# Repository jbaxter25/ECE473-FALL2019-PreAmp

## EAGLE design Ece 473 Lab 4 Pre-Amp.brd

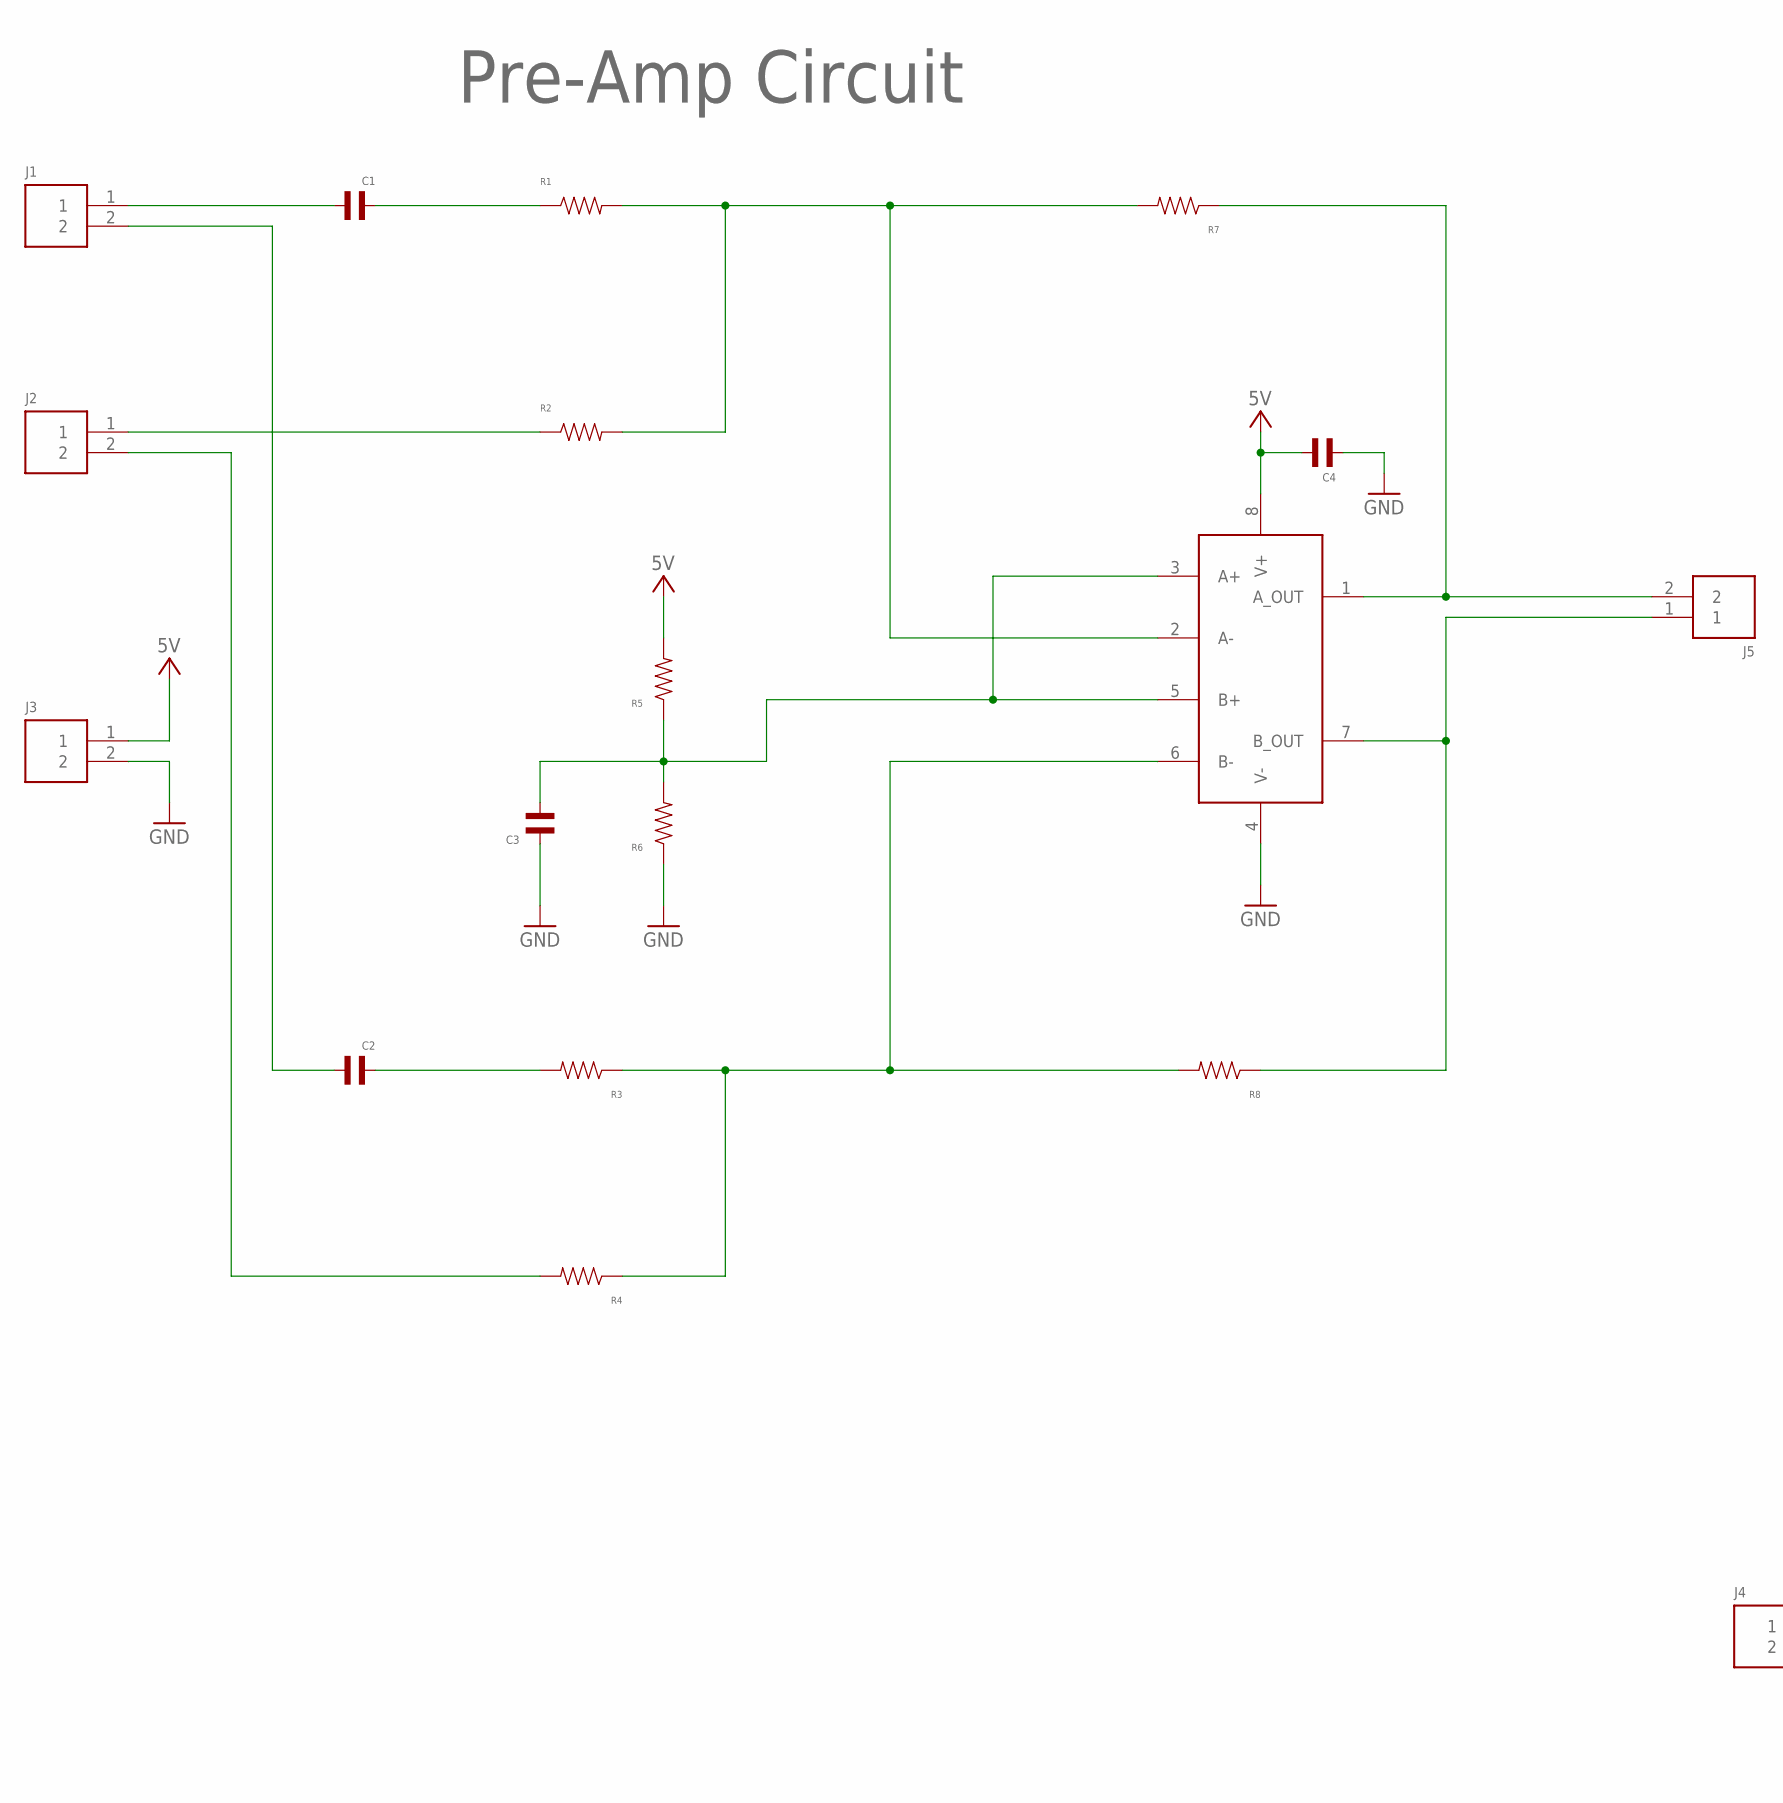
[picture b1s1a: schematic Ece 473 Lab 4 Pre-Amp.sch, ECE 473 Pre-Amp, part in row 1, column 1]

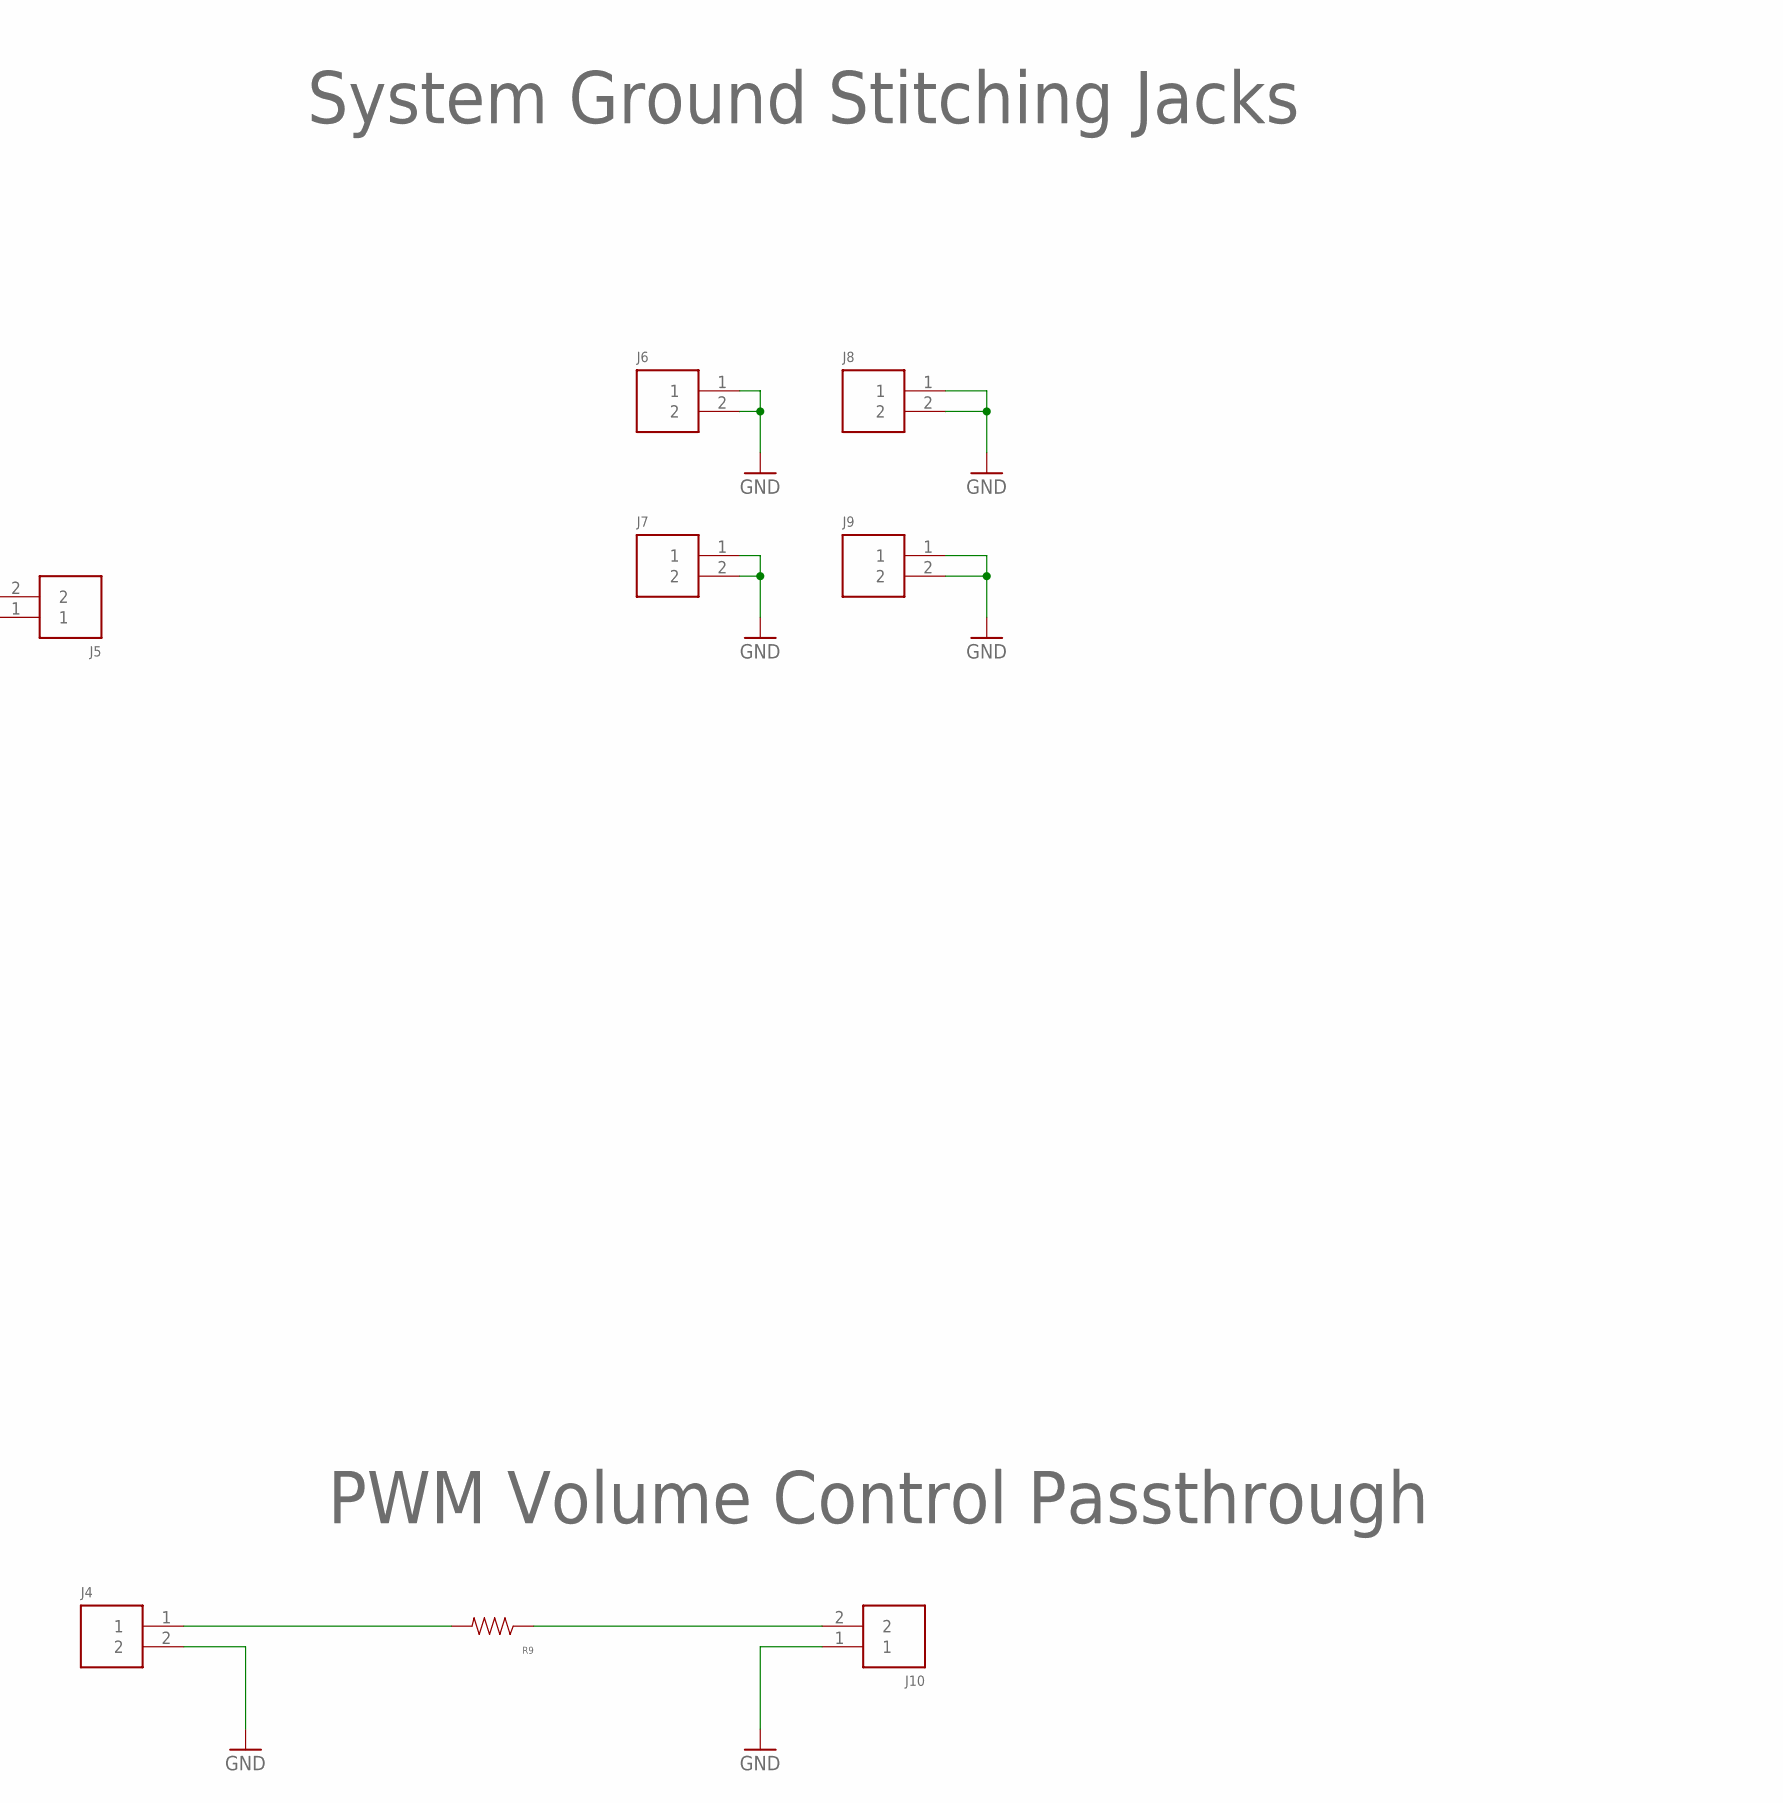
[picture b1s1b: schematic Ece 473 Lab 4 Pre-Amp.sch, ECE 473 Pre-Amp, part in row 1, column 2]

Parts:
C1, C2, C3, C4: 0.1uF; CAP_THROUGH-HOLE
J1, J2, J3, J4, J5, J6, J7, J8, J9, J10: 2x1; HDRV2W64P254_1X2_467X234X838B
R1: 200k; RESISTOR_THROUGH-HOLE
R2, R4: 3k; RESISTOR_THROUGH-HOLE
R3: RESISTOR_THROUGH-HOLE
R5, R6, R9: 100k; RESISTOR_THROUGH-HOLE
R7, R8: 10k; RESISTOR_THROUGH-HOLE
U1: LMC6032; PDIP-8PIN

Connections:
5V: C4.2, J3.1, R5.2, U1.8 (V+)
GND: C3.1, C4.1, J3.2, J4.2, J6.1, J6.2, J7.1, J7.2, J8.1, J8.2, J9.1, J9.2, J10.1, R6.1, U1.4 (V-)
unnamed: C3.2, R5.1, R6.2, U1.3 (A+), U1.5 (B+)
unnamed: J2.1, R2.1
unnamed: C1.1, J1.1
unnamed: C1.2, R1.1
unnamed: J2.2, R4.2
unnamed: R1.2, R2.2, R7.2, U1.2 (A-)
unnamed: J5.2, R7.1, U1.1 (A_OUT)
unnamed: J5.1, R8.1, U1.7 (B_OUT)
unnamed: C2.1, J1.2
unnamed: C2.2, R3.2
unnamed: R3.1, R4.1, R8.2, U1.6 (B-)
unnamed: J4.1, R9.2
unnamed: J10.2, R9.1

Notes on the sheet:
PWM Volume Control Passthrough
Pre-Amp Circuit
System Ground Stitching Jacks

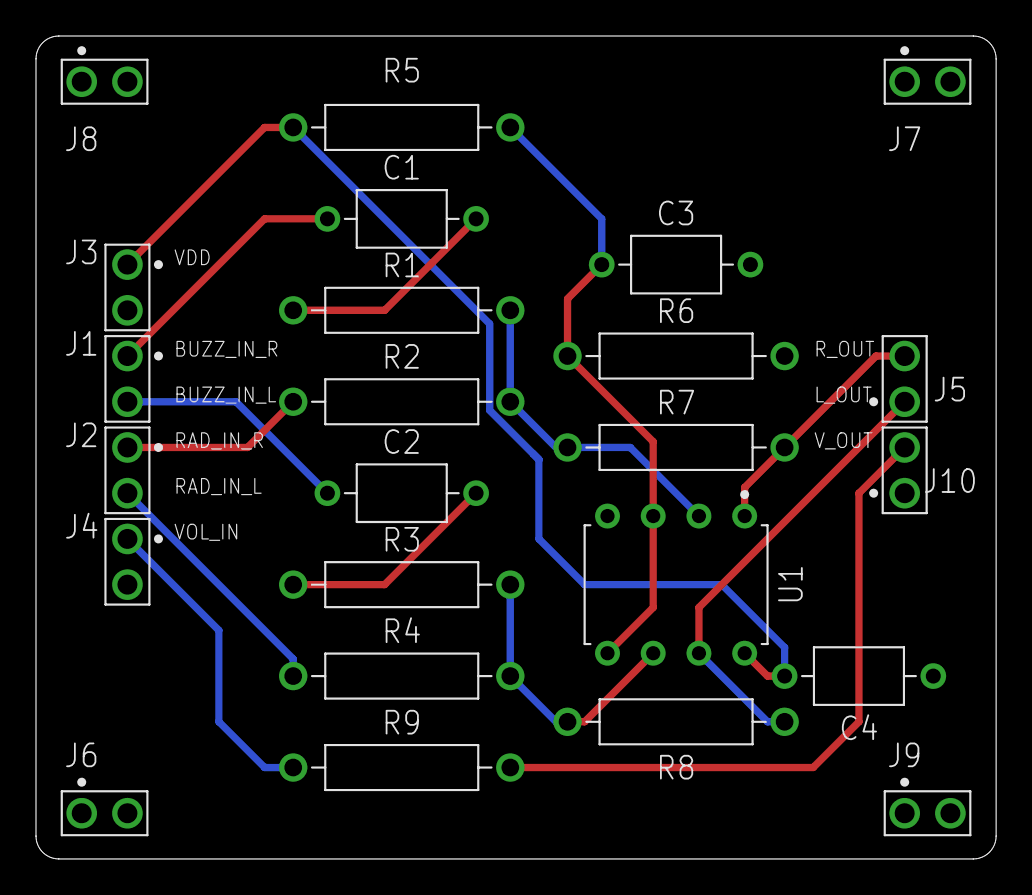
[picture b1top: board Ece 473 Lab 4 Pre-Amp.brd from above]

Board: 2 copper layers, 53.3 x 45.7 mm, 24 parts (0 on the bottom side), 15 nets.

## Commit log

2019-11-10 Initial commit.
2019-11-11 Have fun!
2019-11-11 Added schematic PDF and deleted eagle script outputs.
